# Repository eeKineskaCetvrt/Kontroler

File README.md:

# Spojko - Open [hardware,software]

Spojko je skup elektronskih ploča zajedno sa pripadajućim programima.
## 

Proizašao iz potrebe brzog razvoja novih uređaja i sistema koristeći nove miniPC(Raspberry Pi, BananaPi, Asus Tinker Board) i mikrokontroler(Arduino, ESP) platforme.

Zašto smo se opredelili za open-hardware i open-software?

Šta je open-hardware i open-software?

**Open Hardware**

```sh

Open Hardware, je elektrononski ili kompjuterski hardware napravljen od tehnickih i drugih informacija koje mogu biti kopirane i licencirane ali se ipak daju javnosti besplatno. Takve informacije mogu da budu u vidu dokumentacije, šematskih crteža, tehničkih crteža, liste delova itd.

```

  **Open Software**

```sh

Open-source software (OSS) je kompjuterski program čiji je osnovni kod dat javnosti sa licencom kojom se držaocu licence daje pravo da kod studira, menja, i distribuira trećim licima.

```

Pogledajmo principe OPEN sveta:

**Otvorena razmena**

Možemo naučiti više ako je nam je informacija dostupna. Besplatna razmena je kritična za kreiranje atmosfere gde je ljudima dato da koriste postojeće informacije za kreiranje novih ideja.

**Saradjivanje**

Kada smo slobodni da saradjujemo, mi kreiramo. Zajedno možemo rešiti probleme koje sam čovek, kao pojedinac, ne bi mogao.

**Brzi prototip**

Brzi prototip može dovesti do brzog neuspeha ali svakim novim experimentom se unapredjujemo. Kada smo slobodni da experimentišemo učeći iz konstantnog niza stalno idemo napred.

**Zajednica**

Zajednice se osnivaju oko zajedničkih interesa. One donose raznovrsnost ideja i dele posao. Zajedno, globalna zajednica može kreirati van domašaja pojedinca. Množi se napor i deli se posao.

## Struktura projekta

Projekat u osnovi se deli na:

* Kontroler - Hardware

* Kontroler - Software

* Kontroler - Example

## Doprinesi

* Kreiraj svoju granu

* Unapredi izmene

* Postavi

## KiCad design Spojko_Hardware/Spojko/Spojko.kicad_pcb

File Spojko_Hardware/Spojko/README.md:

# Spojko_Hardware

<<<<<<< HEAD
Ovoj PCB je doveo do imena Spojka.
=======
Ovoj PCB je doveo do imena Spojko!
>>>>>>> develop

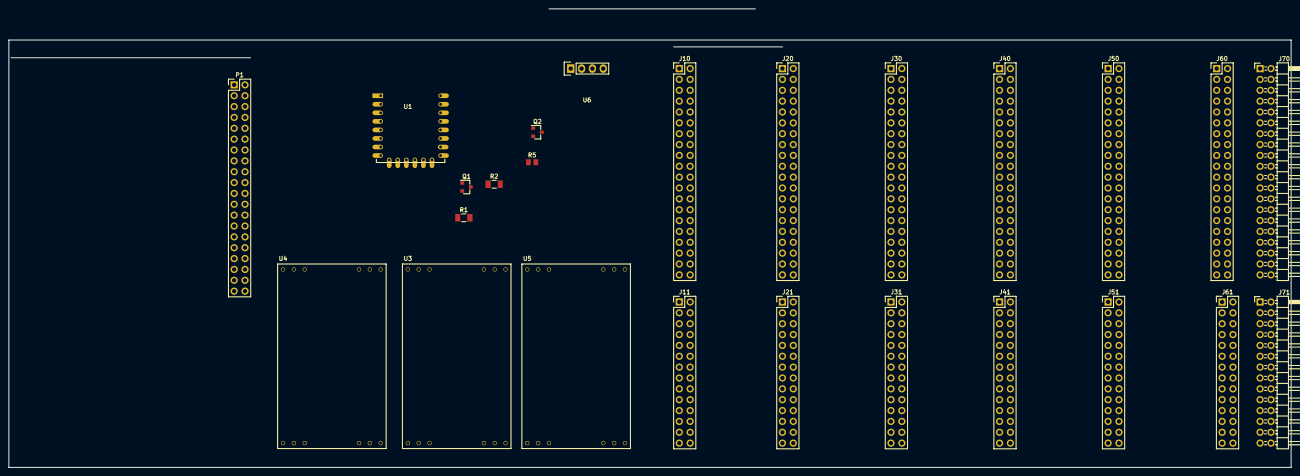
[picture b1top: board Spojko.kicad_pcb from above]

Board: 2 copper layers, 300.0 x 107.3 mm, 25 parts (0 on the bottom side), 28 nets, no tracks yet.

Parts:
J10, J20, J30, J40, J50, J60: Conn_02x20; PinHeader_2x20_P2.54mm_Vertical
J11, J21, J31, J41, J51, J61: Conn_02x14; PinHeader_2x14_P2.54mm_Vertical
J70: Conn_02x20; PinHeader_2x20_P2.54mm_Horizontal
J71: Conn_02x14; PinHeader_2x14_P2.54mm_Horizontal
P1: Raspberry_Pi; PinHeader_2x20_P2.54mm_Vertical
Q1, Q2: BSS138; SOT-23
R1, R2: 10K; R_1206_3216Metric
R5: 10K; R_0805_2012Metric
U1: ESP-12E
U3, U4, U5: vLM2596; Napajanje_5V
U6: DHT11; DHT22_Temperature_Humidity

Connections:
5VMCU: P1.2, P1.4, U3.4
+3V3: J11.21, J11.22, J11.23, J11.24, J21.21, J21.22, J21.23, J21.24, J31.21, J31.22, J31.23, J31.24, J41.21, J41.22, J41.23, J41.24, J51.21, J51.22, J51.23, J51.24, J61.21, J61.22, J61.23, J61.24, J71.21, J71.22, J71.23, J71.24, Q1.1, Q2.1, R1.2, R2.2, U1.8, U5.4
+5V: J11.13, J11.14, J11.15, J11.16, J11.17, J11.18, J21.13, J21.14, J21.15, J21.16, J21.17, J21.18, J31.13, J31.14, J31.15, J31.16, J31.17, J31.18, J41.13, J41.14, J41.15, J41.16, J41.17, J41.18, J51.13, J51.14, J51.15, J51.16, J51.17, J51.18, J61.13, J61.14, J61.15, J61.16, J61.17, J61.18, J71.13, J71.14, J71.15, J71.16, J71.17, J71.18, U4.4
+24V: J11.1, J11.2, J11.3, J11.4, J11.5, J11.6, J21.1, J21.2, J21.3, J21.4, J21.5, J21.6, J31.1, J31.2, J31.3, J31.4, J31.5, J31.6, J41.1, J41.2, J41.3, J41.4, J41.5, J41.6, J51.1, J51.2, J51.3, J51.4, J51.5, J51.6, J61.1, J61.2, J61.3, J61.4, J61.5, J61.6, J71.1, J71.2, J71.3, J71.4, J71.5, J71.6, U3.2, U4.2, U5.2
GND: J10.17, J10.18, J10.21, J10.22, J10.27, J10.28, J10.33, J10.34, J10.39, J10.40, J11.19, J11.20, J11.25, J11.26, J11.27, J11.28, J20.17, J20.18, J20.21, J20.22, J20.27, J20.28, J20.33, J20.34, J20.39, J20.40, J21.19, J21.20, J21.25, J21.26, J21.27, J21.28, J30.17, J30.18, J30.21, J30.22, J30.27, J30.28, J30.33, J30.34, J30.39, J30.40, J31.19, J31.20, J31.25, J31.26, J31.27, J31.28, J40.17, J40.18, J40.21, J40.22, J40.27, J40.28, J40.33, J40.34, J40.39, J40.40, J41.19, J41.20, J41.25, J41.26, J41.27, J50.17, J50.18, J50.21, J50.22, J50.27, J50.28, J50.33, J50.34, J50.39, J50.40, J51.19, J51.20, J51.25, J51.26, J60.17, J60.18, J60.21, J60.22, J60.27, J60.28, J60.33, J60.34, J60.39, J60.40, J61.19, J61.20, J61.25, J61.26, J70.17, J70.18, J70.21, J70.22, J70.27, J70.28, J70.33, J70.34, J70.39, J70.40, J71.19, J71.20, J71.25, J71.26, P1.6, P1.9, P1.14, P1.20, P1.25, P1.30, P1.34, P1.39, R5.2, U1.9, U3.3, U4.3, U5.3, U6.4
GND24V: J11.7, J11.8, J11.9, J11.10, J11.11, J11.12, J21.7, J21.8, J21.9, J21.10, J21.11, J21.12, J31.7, J31.8, J31.9, J31.10, J31.11, J41.7, J41.8, J41.9, J41.10, J51.7, J51.8, J51.9, J51.10, J61.7, J61.8, J61.9, J61.10, J71.7, J71.8, J71.9, J71.10, U3.1, U4.1, U5.1
GPIO26: P1.37, U1.6, U6.2
unnamed: J10.1, J10.2, J20.1, J20.2, J30.1, J30.2, J40.1, J40.2, J50.1, J50.2, J60.1, J60.2, J70.1, J70.2
unnamed: J10.3, J10.4, J20.3, J20.4, J30.3, J30.4, J40.3, J40.4, J50.3, J50.4, J60.3, J60.4, J70.3, J70.4
unnamed: J10.5, J10.6, J20.5, J20.6, J30.5, J30.6, J40.5, J40.6, J50.5, J50.6, J60.5, J60.6, J70.5
unnamed: J10.7, J10.8, J20.7, J20.8, J30.7, J30.8, J40.7, J40.8, J50.7, J50.8, J60.7, J60.8, J70.7, J70.8
unnamed: J10.9, J10.10, J20.9, J20.10, J30.9, J30.10, J40.9, J40.10, J50.9, J50.10, J60.9, J60.10, J70.9, J70.10
unnamed: J10.11, J10.12, J20.11, J20.12, J30.11, J30.12, J40.11, J40.12, J50.11, J50.12, J60.11, J60.12, J70.11, J70.12
unnamed: J10.13, J10.14, J20.13, J20.14, J30.13, J30.14, J40.13, J40.14, J50.13, J50.14, J60.13, J60.14, J70.13, J70.14
unnamed: J10.15, J10.16, J20.15, J20.16, J30.15, J30.16, J40.15, J40.16, J50.15, J50.16, J60.15, J60.16, J70.15
unnamed: J31.12, J41.11, J41.12, J51.11, J51.12, J61.11, J61.12, J71.11, J71.12
unnamed: J41.28, J51.27, J51.28, J61.27, J61.28, J71.27, J71.28
unnamed: P1.1, U6.1
unnamed: R1.1, U1.1
unnamed: R2.1, U1.3
unnamed: R5.1, U1.10
RST: J10.19, J10.20, J20.19, J20.20, J30.19, J30.20, J40.19, J40.20, J50.19, J50.20, J60.19, J60.20, J70.19, J70.20, P1.26
RXD: J10.25, J10.26, J20.25, J20.26, J30.25, J30.26, J40.25, J40.26, J50.25, J50.26, J60.25, J60.26, J70.25, J70.26, P1.10, U1.15
SCL: J10.37, J10.38, J20.37, J20.38, J30.37, J30.38, J40.37, J40.38, J50.37, J50.38, J60.37, J60.38, J70.37, J70.38, P1.5, U1.14
SCL1: J10.29, J10.30, J20.29, J20.30, J30.29, J30.30, J40.29, J40.30, J50.29, J50.30, J60.29, J60.30, J70.29, J70.30, Q1.3
SDA: J10.35, J10.36, J20.35, J20.36, J30.35, J30.36, J40.35, J40.36, J50.35, J50.36, J60.35, J60.36, J70.35, J70.36, P1.3, U1.13
SDA1: J10.31, J10.32, J20.31, J20.32, J30.31, J30.32, J40.31, J40.32, J50.31, J50.32, J60.31, J60.32, J70.31, J70.32, Q2.3
TXD: J10.23, J10.24, J20.23, J20.24, J30.23, J30.24, J40.23, J40.24, J50.23, J50.24, J60.23, J60.24, J70.23, J70.24, P1.8, U1.16

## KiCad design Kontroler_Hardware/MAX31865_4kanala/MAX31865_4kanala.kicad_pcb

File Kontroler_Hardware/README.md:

# Kontroler_Hardware

Kontroler hardware(gvožđe) je deo projekta u kome se nalaze šeme i dizajn elektronskih ploča bazirane na OPEN SOURCE [Kicad EDA](http://kicad-pcb.org/) (Electronics Design Automation) razvojnom okruzenju.

## Instalacija

Preuzmite najnoviju verziju Kicad programa [OVDE](http://kicad-pcb.org/download/).

Instalacioni video [Windows](https://www.youtube.com/watch?v=Cu2VlXy-PzM), [Ubuntu](https://www.youtube.com/watch?v=C87Lrf-ipTA).

Korišćenje Github Kicad biblioteka [VIDEO](https://www.youtube.com/watch?v=KNXB4zgupG4).

## Kontroler i Kicad

Glavna primedba većine novih [Kicad](http://kicad-pcb.org/) korisnika je vezana za biblioteke šematskog simbola i footprint-a. Trik je da se koristi samo jedna biblioteka za šematske simbole i jedna za footprint-e. kroz projekat. Na ovaj način promene u osnovnim bibliotekama neće imati uticaj na biblioteke projekta i sa lakoćom će se projekat deliti bez bojazni od pucanja. U nastavku će se ova tema detaljnije pojasniti.

Kicad čuva šematske simbole i footprint-e u pojedinačnim bibliotekama i na vama je da povežete simbol sa pripadajućim footprint-om koristeći jedan od više načina. Ovo dosta odbija ljude, ali veoma lepo radi kada se naviknete.

U staro doba, pre kompjutera, većina dizajnera bi prvo nacrtala **šematski prikaz** pa zatim kreirala **listu materijala** gde bi definisali specifikacije komponenti koje su korišćene i nastavili ka sledećoj fazi izrade elektronskih pločica.

KiCAD prati te korake.

#### Struktura Kontroler pod-projekta

* Kontroler
	* Ime podprojekta
		* 3d_models       // .STEP i .WRL model fajlovi za sve footprint-e
		*  datasheets     // Tehnicka uputsva komponenti
		* gerber         // Završni masinski fajlovi
		* images         // SVG slike i 3d renderi ploča
		* lib_sch        // Biblioteka šematskih simbola
		* lib_fp.pretty  // Biblioteka footprint-a
		* pdf            // Šeme, tehnički crteži, raspored komponenti itd.
		* ReadMeStuff  // Slike i fajlovi potrebni za README file

#### Menadžment biblioteke simbola
Kada crtate šeme pomoću simbola iz Kicad osnovne biblioteke, EESCHEMA stvara lokalnu rezervnu biblioteku pod nazivom  _**podprojekat-cache.lib**_. Kad završite sa crtanjem sheme, kopirajte ovu datoteku u _**lib_sch**_ folder i preimenujte je u _**podprojekat.lib**_, ostala biblioteke simbola mozete obrisati.

Zatim idite na **↳PREFERENCES ↳Component library**, odaberite **↳CURRENT SEARCH PATH LIST**. Da biste uputili na svoj lokalni folder projekta ~ / podprojekta /, kliknite dugme **ADD** (DODAJ) u gornjem pop-up prozoru (NIJE dugme Add u sredini pop-up), i na kraju odaberite _**podprojekat.lib**_. Dodaje se ispod trenutno odabrane biblioteke u listu.

KiCAD čita biblioteke redom, stoga morate odabrati podprojekat.lib i staviti ga na vrh liste pomoću dugmeta UP. Ako postoji sličan simbol u različitim bibliotekama, tada se prva instanca koristi! U ovom trenutku možete ukloniti sve druge navedene biblioteke ili ih zanemariti sve dok osiguravate da svaki simbol koji upotrebljavate je dodat u podprojekat.lib i da se poziva samo iz te datoteke.
Vaš projekt sada koristi samo jednu shematsku biblioteku simbola -_~ / Spojko / lib_sch / podprojekat.lib_ - i sve izmene shematskih biblioteka neće uticati na vaš projekat. Koristeći gore definisanu strukturu, lako je deliti projekat na GitHub-u bez bojazni o sukobu   u biblioteci.

### Povezivanje footprint-a sa simbolom
Postoji nekoliko načina za to, ali u suštini, dok je kursor iznad komponente kojoj želimo dodeliti footprint _pritisnemo_ **E** slovo na tastaturi i dodelimo footprint iz biblioteke. Od kad je KiCAD premestio biblioteke za footprint-e na GitHub, mnogima je to bio uzrok problema. Kao prvo, sve su biblioteke smeštene online, a KiCAD ih treba tražiti svaki put kada ga pokrenete. Za one koji ne menjaju ovo ponašanje, usporava se program pri pokretanju, ako niste povezani sa internetom. Online biblioteke su dobra ideja jer se footprint-i konstantno ažuriraju, ali to je siguran način da se pokvari vaš dizajn, recimo, ako je jedan od footprint-a koji se koristi u dizajnu promenjen. Ovo vam se neće odmah prikazati jer ćete morati izričito ponovno pročitati NET list i odabrati opciju promene footprinta pri povlačenju nove liste. Za nekog ko klonira vaš dizajn, a njihova verzija KiCAD-a je unapređena, ili suprotno, to će dovesti do problema.
Rešenje je klonirati sve KiCAD biblioteke na lokalno mesto na računaru, a zatim usmeriti KiCAD na tu lokaciju. No, kada to učinite, ona negira prednost pristupa ažuriranim bibliotekama. Mislim da ne postoji idealan način da to funkcioniše, ali evo što radi za nas.
Klonirati GitHub biblioteku na lokalni računar, i držati ih obnovljenom redovnim povlačenjem. To nam pomaže da koristimo postojeće footprint-e ili ih menjamo kako bi odgovarali našim potrebama. Naš projekat ne koristi bilo koju od tih kloniranih biblioteka direktno. Umesto toga, generišemo biblioteku sa podacima o projektu koja sadrži sve footprint-e (__~ / podprojekat / lib_fp.pretty__) koji se koriste u projektu. Još jednom, to osigurava da kada se projekat dobije kloniranjem, svi pravi footprint-i su već dostupni bez zavisnosti o spoljasnim bibliotekama.

### Kako da napravimo KiCad footprint-e lokalnim i Projekat jedinstvenim
Započnite kloniranjem (iz GitHub-a) KiCAD footprint-a na vaš računar. To je najbolje učiniti korišćenjem _menadžera za biblioteke footprint-a_, iz programa __PCBnew. U mom slučaju, ja sam ga klonirao u ~ / kicad_sources / library-repos. U programu __PCBnew KiCAD__ odaberite __↳PREFERENCES ↳CONFIGURE PATHS__ i _uredite_ __KISYSMOD__ da biste uputili na lokalnu putanju biblioteke (_~ / kicad_sources / library-repos_).
1
1
1      Ovde sliku trebalo bi staviti!!!
1
1
1
U nekim slučajevima možda će biti potrebni dodatni koraci kako bi stvari funkcionisale. Odaberite **↳PREFERENCES ↳FOOTPRINT LIBRARIES MANAGER** i odredite mesto datoteke "_fp-lib-table_" koje koristi PCBnew. Ovo je tekstualna datoteka koja govori PCBnew gde potražiti biblioteke footprint-a na Githubu, lokalnom putu i sl. Otvorite ovu datoteku u uređivaču teksta i proverite upotrebljava li KISYSMOD put. Ako ne, učinite pretraživanje i zamenite sve instance trenutnog puta sa KISYSMOD.
1
1
1
1 slikaaaaa
1
1
Sada možete urediti svaki šematski simbol i dodati mu footprint - bilo iz EESCHEMA ili pomoću samostalnog Cvpcb modula. Nakon što su dodeljeni svi footprint-a, pobrinite se da ponovno generišete NET list pre prelaska na PCBnew.

Sada možete započeti PCBnew i pročitati NET list. Odaberite način rada: ikonu footprint, a zatim desni klik na bilo koji nivo otiska, odaberite opciju **↳Globalna širenja i mjesto ↳ Proširite** sve footprinte.
Ovo širi sve footprinte, iy gomile u kojoj na kojoj se pojave posle povlačenja NET liste olakšavajuči odabir i njihovo premeštanje. Kada završite sa izgledom ploče, a svi su vam footprint-i zaključani, _odaberite_ **FILE ↳ Arhive footprints ◦ Kreiraj biblioteku i footprint-e**  _navedite_ putanju za **/ naziv.pretty** u vašem projektu (_~ / podprojekat / lib_fp.pretty_). Ovo kopira sve footpint-e koji se koriste u vašem projektu u ciljanu datoteku.
Zatim kliknite **Preferences↳Wizard_FilesFootprint LibrariesFiles** na mom računaru (idite na ~ / podprojekat / lib_fp.pretty) i provjerite jeste li odabrali **"Samo za tekući projekt"** prije nego što potvrdite sa **Finish**. U ovom trenutku koristili ste footprinte iz globalnih biblioteka KiCAD-a i primenili ih na šematske simbole, napravili NET list, uvezli NET list u PCBnew, postavili footprint-e i rutovali ploču, napravili arhivu svih upotrijebljenih stopala i konfigurirali PCBnew za korištenje da arhivska knjižnica.

Zatim se vratite nazad na EESCHEMA i uredite fooprint svakog simbola da biste ga uputili novu putanju _lib_fp.pretty_ umesto lokalnog skladišta GitHub-a na računaru. Najlakši način za to je da otvorite .SCH datoteku u uređivaču teksta i pretražujete / zamenite. U našem sadašnjem primeru zamenit ćemo primerke kao što su _"Capacitors_ThroughHole"_ ili _"Resistors_ThroughHole"_ ili _"LEDs"_ s našom lokalnom datotekom u projektu _"lib_fp"_
Otvorite šematski prikat zadnji put, generišite sveži NET list, otvorite PCBnew, povucite novi NET list, ali ovaj put odaberite opciju CHANGE pod Foot Footprint. Vaš izgled ploče sada koristi zagrade spremljene u datoteci lib_fp.pretty, a promene u bibliotekama KiCAD-a neće uticati na projekat.

## Zaključak
Ovo sve može zvučati pomalo zbunjujuće u početku, ali vremenom postaje vrlo lako i možete eliminisati neke korake. Na primer, već imamo biblioteku za većinu zajedničkih delova koje upotrebljavamao, kopirajte ove footprint-e pre početka novog projekta. Tokom vremena, kako postaje sve bolji, počet ćete graditi svoje šematske simbole i footprint-e, umesto korišćenja spoljšnih verzija. Kao što sam rekao na početku, nije savršeno, i za mene taj proces radi jako dobro. Ako imate komentare ili predloge o tome da to učinite bolje, kreirajte svoju granu, unapredite, postavite.

##Zahvalnica

**Anool Mahidharia**, na divnom tekstu!!! Hackaday / *KiCAD Best Practices: Library Management*

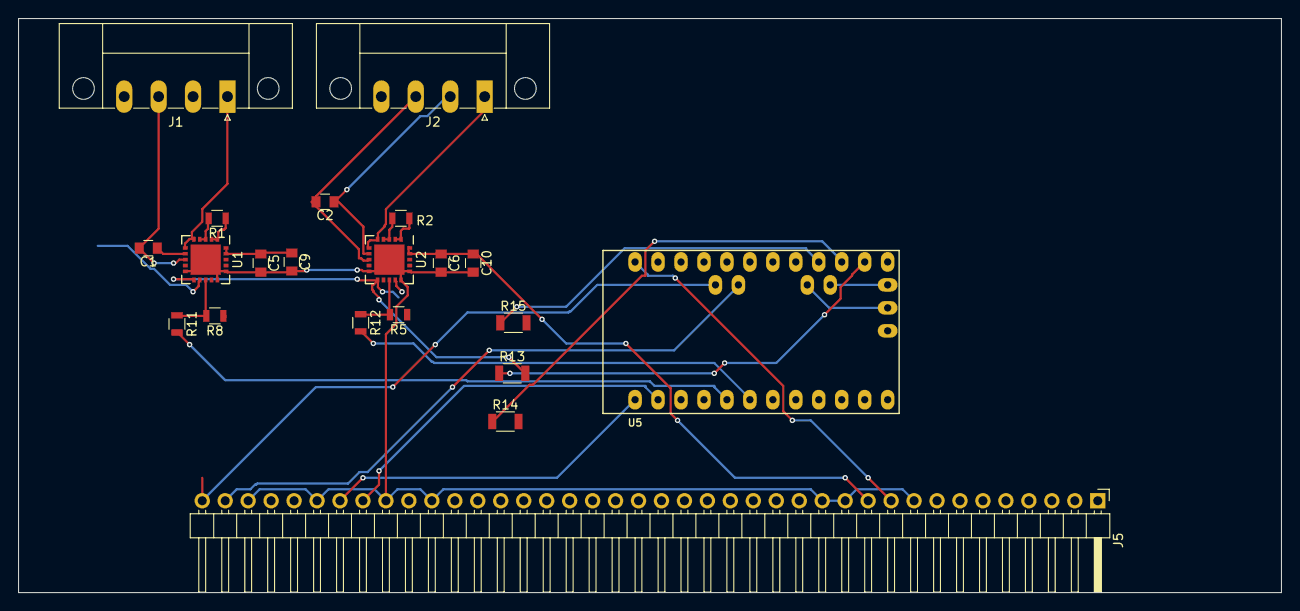
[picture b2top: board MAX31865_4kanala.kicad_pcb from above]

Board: 2 copper layers, 139.7 x 63.5 mm, 21 parts (0 on the bottom side), 29 nets.

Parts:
C1, C2, C5, C9: 0.1uF 25V, X7R; C_0805
C6, C10: C; C_0805
J1, J2: CONN_01X04; PhoenixContact_MC-GF_04x3.81mm_Angled_ThreadedFlange_MountH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
J5: CONN_01X40; Pin_Header_Angled_1x40_Pitch2.54mm
R1, R2: 400; R_0805
R5, R8, R11, R12: 150; R_0805
R13, R14, R15: 150; R_1206
U1, U2: MAX31865; QFN-20-1EP_5x5mm_Pitch0.65mm
U5: ProMini; pro_mini

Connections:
/FORCE0-: J1.4, U1.9
/FORCE1-: J2.4, U2.9
/IFORCE0+: J1.1, U1.5, U1.6
/IFORCE1+: J2.1, U2.5, U2.6
/RTDIN0+: C1.1, J1.2, U1.7
/RTDIN0-: C1.2, J1.3, U1.8
/RTDIN1+: C2.1, J2.2, U2.7
/RTDIN1-: C2.2, J2.3, U2.8
CS0: R11.2, U5.5
CS1: R12.2, U5.6
GND: C5.2, C6.2, C9.2, C10.2, J5.9, J5.12, J5.13, J5.30, J5.32, J5.35, J5.38, U1.10, U1.15, U1.16, U1.21, U2.10, U2.15, U2.16, U2.21
unnamed: R1.1, U1.1, U1.2
unnamed: R1.2, U1.3, U1.4
unnamed: R2.1, U2.1, U2.2
unnamed: R2.2, U2.3, U2.4
unnamed: R8.2, R11.1, U1.13
unnamed: R5.2, R12.1, U2.13
unnamed: R13.1, U5.14
unnamed: R13.2, U1.11, U2.11
unnamed: R14.1, U5.15
unnamed: R14.2, U1.14, U2.14
unnamed: R15.1, U5.16
unnamed: R15.2, U1.12, U2.12
RX: J5.33, U5.2
SCL: J5.40, U5.26
SDA: J5.39, U5.25
TX: J5.34, U5.1
VCC: J5.10, U5.24
VDD: C5.1, C6.1, C9.1, C10.1, J5.11, R5.1, R8.1, U1.19, U1.20, U2.19, U2.20

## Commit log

2017-09-26 First
2017-09-26 FirstCommit
2017-09-30 Popravljena greska u konektorima
2017-10-01 Spojko zavrsen, valjda
2017-10-01 Ponovno rutovanje i izbacivanje konektora...
2017-10-02 Izmene predlozi matori
2017-10-10 Set theme jekyll-theme-architect
2018-04-06 Added gif main ReadMe
2018-04-06 Added gif
2018-04-09 Prepravke
2018-04-09 Edit
2018-04-09 New picture
2018-04-09 Add picture
2018-04-09 TitleChange
2018-04-09 Novi markdown test software
2018-04-09 test
2018-04-09 New ReadMeee
2018-04-09 Changed project structure
2018-04-09 Header change
2018-04-09 Obrisao eng..
2018-04-09 Change...
2018-04-09 Name change
2018-04-10 ReadMe edit
2018-04-10 Zahvalnica
2018-04-15 Promene dimenzija i update readme
2018-04-15 ReadMe zahvalnica
2018-04-15 Fix max31865 lib
2018-04-15 Dodati ReadMe u sve kartice
2018-04-16 Dodat template
2018-04-16 Novi Template
2018-04-18 Nesto
2018-04-18 Dodata slika
2018-04-19 Putanje slike
2018-04-19 Set theme jekyll-theme-midnight
2018-04-19 Set theme jekyll-theme-cayman
2018-04-19 Create LICENCE
2018-04-19 Dodato MadeWith_Kontroler
2018-04-19 Iybacena meritokratija
2018-04-20 Change PowerConnector
2018-04-23 Puno izmena
2018-04-23 Dodao kondenzator
2018-04-26 Rasturanje zbog 10x10 dimenzije
2018-04-26 Added new main picture
2018-04-26 Sredjen naslov
2018-04-28 Deleted PCB Spojko
2018-04-29 FIX Spojko
    fp-lib-table
    sym-lib-table
2018-05-14 NewTemplates
2018-05-15 Finish templates
2018-05-16 Change main Kontroler picture
2018-06-03 Izmene v5
2018-08-07 Spojko returns
2018-08-11 Pre Develope
2018-08-11 Update develope
2018-08-13 Aaaa
2018-08-16 NewSpojko
